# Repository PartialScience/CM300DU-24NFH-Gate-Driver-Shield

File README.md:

# CM300DU-24NFH IGBT Gate Driver / Protection Shield

KiCad files for a small daughter-board that mounts directly over a Mitsubishi
**CM300DU-24NFH** dual IGBT module to provide gate drive coupling and
collector–emitter transient protection. Designed for use in my first
[DRSSTC](https://en.wikipedia.org/wiki/Tesla_coil#Solid-state_Tesla_coil)
build.

## What the board does

The shield carries four electrically isolated circuits on a single PCB:

- **Two gate-drive networks** — one per IGBT in the module. Each takes the
  output of a gate-drive transformer and feeds the gate through an
  anti-parallel resistor / Schottky diode pair. The asymmetric turn-on vs.
  turn-off impedance adds a small amount of switching hysteresis, which
  prevents both IGBTs in a half-bridge from being briefly in conduction at the
  same time and shorting the DC bus.
- **Two collector–emitter clamp networks** — one per IGBT. Each is a string of
  series TVS diodes across the C–E terminals to catch fast switching
  transients that the main bus snubber may not absorb quickly enough,
  protecting the IGBT from voltage spikes during turn-off.

Mounting the protection on its own PCB directly above the module keeps the
loop area between the clamps and the IGBT terminals as small as possible,
which is what makes the clamps actually effective at high di/dt.

## Key components

| Function | Part |
| --- | --- |
| IGBT module (footprint) | Mitsubishi CM300DU-24NFH |
| Primary TVS (C–E clamp string) | Vishay 1.5KE220CA (×8) |
| Secondary TVS | P6KE30CA (×2) |
| Gate-drive Schottky | 1N5819 (×2) |
| Gate trim pot | Bourns 3362X-1-100LF (×2) |
| Gate-drive headers | Molex 22-01-2021 (×2) |
| Output headers | Molex 171857-0002 (×2) |

See [`bom.csv`](bom.csv) for the full bill of materials.

## Repository contents

- `Gate_Driver.kicad_*` — KiCad 7+ project (schematic, PCB, design rules)
- `PowerIGBTs.kicad_sym` — symbol library for the IGBT module
- `Library.pretty/` — footprint library
- `CM300DU-24NFH Outline*.dxf` — mechanical outline of the IGBT module
- `Gate_Driver*.step` — 3D models of various board revisions
- `Custom-Connector.stp` — 3D model of the gate-drive connector
- `BoardTop.png`, `Logo.png` — render and silkscreen artwork
- `bom.csv` — bill of materials

## License

Released under the MIT License — see [`LICENSE`](LICENSE).

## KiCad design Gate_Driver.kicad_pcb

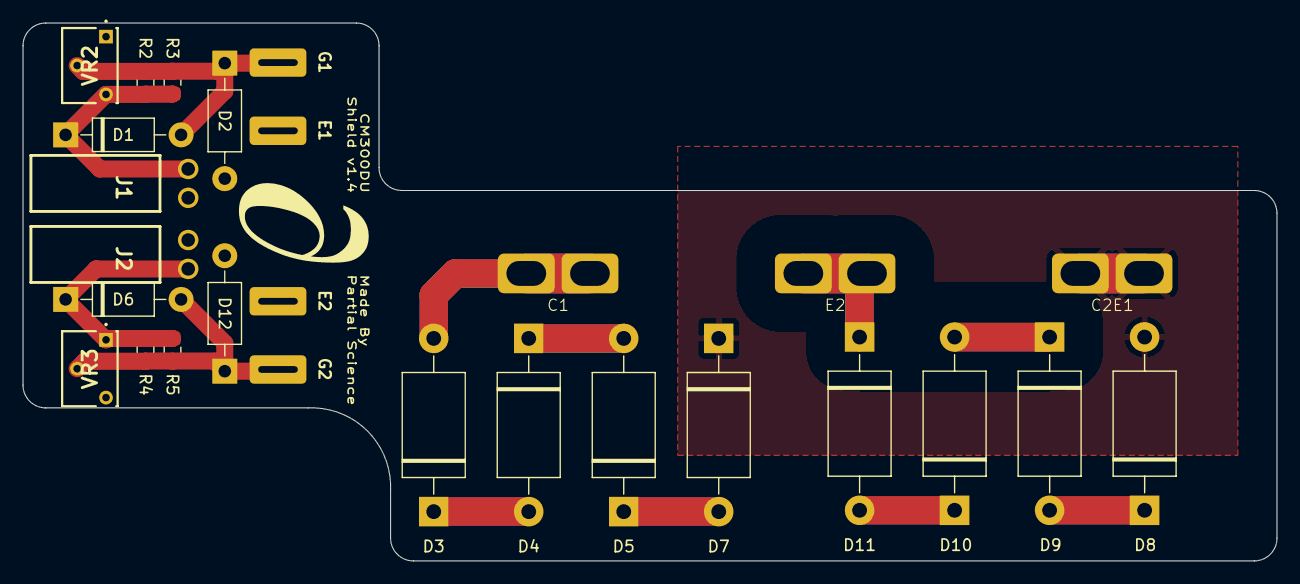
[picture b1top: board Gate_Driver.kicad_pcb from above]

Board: 2 copper layers, 110.3 x 47.3 mm, 24 parts (0 on the bottom side), 15 nets.

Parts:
C1: C1; Custom CM300DU Terminal Connector
C2E1: C2E1; Custom CM300DU Terminal Connector
D1, D6: 1N5819; D_DO-41_SOD81_P10.16mm_Horizontal
D2, D12: P6KE30CA; D_DO-41_SOD81_P10.16mm_Horizontal
D3, D4, D5, D7, D8, D9, D10, D11: 1.5KE220CA; D_DO-201AE_P15.24mm_Horizontal
E2: E2; Custom CM300DU Terminal Connector
J1, J2: 171857-0002
Q1: CM300DU-24NFH
R2, R3, R4, R5: R; R_0805_2012Metric_Pad1.20x1.40mm_HandSolder
VR2, VR3: 3362X-1-100LF; 3362X1100LF

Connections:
unnamed: C1.1, D3.2 (A2)
unnamed: C2E1.1, D7.1 (A1), D8.2 (A2)
unnamed: D1.2 (A), D2.1 (K), Q1.1 (G1), R2.2, R3.2, VR2.2
unnamed: D1.1 (K), J1.2, R2.1, R3.1, VR2.3
unnamed: D2.2 (A), J1.1, Q1.2 (E1)
unnamed: D3.1 (A1), D4.2 (A2)
unnamed: D4.1 (A1), D5.2 (A2)
unnamed: D5.1 (A1), D7.2 (A2)
unnamed: D6.1 (K), J2.1, R4.1, R5.1, VR3.1
unnamed: D8.1 (A1), D9.2 (A2)
unnamed: D10.1 (A1), D11.2 (A2)
unnamed: D9.1 (A1), D10.2 (A2)
unnamed: D11.1 (A1), E2.1
unnamed: D12.2 (A), J2.2, Q1.3 (E2)
unnamed: D6.2 (A), D12.1 (K), R4.2, R5.2, VR3.2

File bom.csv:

"Reference","Value","Datasheet","Footprint","Qty","DNP","Mouser Number","Mouser Part Number"
"C1","C1","~","Connector_Wire:SolderWirePad_1x01_SMD_5x10mm","1","","",""
"C2E1","C2E1","~","Connector_Wire:SolderWirePad_1x01_SMD_5x10mm","1","","",""
"D1,D6","1N5819","http://www.vishay.com/docs/88525/1n5817.pdf","Diode_THT:D_DO-41_SOD81_P10.16mm_Horizontal","2","","",""
"D2,D12","P6KE30CA","~","Diode_THT:D_DO-41_SOD81_P10.16mm_Horizontal","2","","821-P6KE30CA ",""
"D3,D4,D5,D7,D8,D9,D10,D11","1.5KExxCA","https://www.vishay.com/docs/88301/15ke.pdf","Diode_THT:D_DO-201AE_P15.24mm_Horizontal","8","","",""
"E2","E2","~","Connector_Wire:SolderWirePad_1x01_SMD_5x10mm","1","","",""
"J1,J2","171857-0002","http://www.molex.com/webdocs/datasheets/pdf/en-us//171857000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","171857-0002","2","","538-171857-0002",""
"Q1","~","","Library:CM300DU-24NFH","1","","",""
"R1,R5","5.1","~","Resistor_THT:R_Axial_DIN0207_L6.3mm_D2.5mm_P10.16mm_Horizontal","2","","",""
"R2,R3","R","~","Resistor_THT:R_Axial_DIN0207_L6.3mm_D2.5mm_P10.16mm_Horizontal","2","DNP","",""

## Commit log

2026-01-05 inital commit
2026-01-18 Implment up to V1.1
2026-01-18 Remove all ignored files from the repository
2026-01-19 Design done with smaller cap
2026-01-19 minor tweaks
2026-01-20 Added pots and re-routed
2026-01-20 Polish design and finish routing
2026-01-27 Clean up bom and minor PCB changes
2026-01-27 Route longer C1-E1 trace as a filled zone
2026-01-27 Update .gitignore to exclude generated production files
2026-04-27 Refresh PCB UUIDs, bump mask-to-copper clearance, regenerate iBOM
    - Gate_Driver.kicad_pro: solder_mask_to_copper_clearance 0 -> 0.005,
    add ngspice block written by KiCad on first simulation open
    - Gate_Driver.kicad_pcb: footprint UUID churn from a re-save
    - bom/ibom.html: regenerated interactive BOM
2026-04-27 Rewrite README with full project description
    Replace the 2-line stub with a description of the CM300DU-24NFH gate-driver
    shield: the four isolated circuits (two gate-drive transformer networks
    with hysteresis-shaping diode/resistor pairs, two collector-emitter TVS
    strings), a key-parts table, and a guide to the repo layout.
